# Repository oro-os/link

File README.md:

<div align="center">
	
</div>

# Oro Link

This is the Oro Link project, a set of custom PCBs, firmware, and server
infrastructure for the testing of the Oro Operating System via CI/CD pipelines.

The link is a physical board that interfaces with the ports and headers
of supported computers, devices, and boards, and runs firmware to obtain builds of
the Oro kernel and associated modules to send to the System Under Test (SUT)
for automated testing and reporting.

The Oro Link allows contributors to the Oro project direct access - via
pull requests - to test changes directly on real hardware
alongside emulated environments, allowing for changes to be tested
against niche or problematic hardware configurations.

## Project Layout

All PCBs are located in `pcb/`, where all of the server infrastructure and firmware for the PCBs
is located in `firmware/` since it's a workspace with some local dependencies (e.g. the protocol
spoken between the boards and the CI/CD daemon).

# License

<div align="center">
	
</div>

Part of the Oro Operating System project.

The Oro Link is released to the public, WARRANTY FREE
and provided AS IS. The Oro project and its contributors are NOT
responsible for any damages caused by the purchase, assembly, or operation
of the device, under any circumstances.

The Oro Link's PCB and associated custom footprints are released
under the [MIT License](LICENSE).

Unless otherwise specified, all Oro Link firmware (software code)
and all other materials are licensed under the same license.

Firmware dependencies are under their respective licenses.

The _Enter Command_ font used in part for text display is released CC-BY-4.0
by [Font End Dev (jeti)](https://fontenddev.com).

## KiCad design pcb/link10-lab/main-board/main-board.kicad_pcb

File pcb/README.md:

# Oro Link PCBs

The Oro Link PCBs are custom boards meant to interface with the
CI/CD daemon, which itself works with (at the moment, solely) GitHub
Actions runners that it manages.

These PCBs are open source and licensed under the license found in the
root of this repository.

All PCBs are designed in KiCad 7, with some technical sketches
designed in FreeCad.

There are some "legacy" PCBs here that haven't been converted to
self-standing projects (that use the `.lib/` folder). Further,
some of these PCBs are specific to individual rigs and may not
be interesting to most people.

## `link-rpi-base`

This is the base board for Raspberry Pi test rigs. It hosts
the microcontroller, network interface, etc. as well as a
board-to-board connector that interfaces with one of the
daughter boards (R-Pi version specific).

## `link-x86-obt`

> **NOTE:** This project file is a _legacy_ PCB that hasn't
> been converted to use the common components/footprints library
> in `.lib/`. You will be able to view the schematic and layout,
> but changes are more difficult to make and manage. Due to this,
> PRs that include changes to this PCB might take longer to merge.

This is the main board for testing x86/x86_64 machines using
the Oro Link CI/CD pipeline. Kernel builds are booted over PXE,
and communication is done primarily through the serial ports.

The board's form factor is designed to be mounted to the front
of an [Open Bench Table](https://openbenchtable.com/) - hence
`*-obt`.

As such, the board has two ethernet connections - one for communication
with the SUT, and the other for communication with the Link daemon.

Please see the [firmware directory](../firmware/link-firmware-x86)
for a block diagram and further explanations.

## `rj45-inverter-h410mb`

> **NOTE:** This is a rig-specific board that is likely uninteresting
> to you. It's meant to fit and cater to a very specific hardware
> configuration that most likely won't match yours. As such, this PCB
> is not required to operate a Link test rig, and probably won't
> be of use unless you match the test rig's build exactly.

> **NOTE:** This project file is a _legacy_ PCB that hasn't
> been converted to use the common components/footprints library
> in `.lib/`. You will be able to view the schematic and layout,
> but changes are more difficult to make and manage. Due to this,
> PRs that include changes to this PCB might take longer to merge.

This board has a board-mounted RJ-45 plug (_not_ socket - THT
mounted plugs were really tricky to find!) that is wired same-side
to an RJ-45 port. It's used on one of the x86 test rigs to keep the
left side of the OBT setup flush, without having an ethernet cable
poking out to the left and causing clearance issues.

## `vga-display-card-h410mb`

> **NOTE:** This is a rig-specific board that is likely uninteresting
> to you. It's meant to fit and cater to a very specific hardware
> configuration that most likely won't match yours. As such, this PCB
> is not required to operate a Link test rig, and probably won't
> be of use unless you match the test rig's build exactly.

> **NOTE:** This project file is a _legacy_ PCB that hasn't
> been converted to use the common components/footprints library
> in `.lib/`. You will be able to view the schematic and layout,
> but changes are more difficult to make and manage. Due to this,
> PRs that include changes to this PCB might take longer to merge.

This board provides power to a [VGA display](https://www.amazon.de/-/en/gp/product/B09ZDK5DMT/ref=ppx_yo_dt_b_search_asin_title?ie=UTF8&psc=1) via a PCIe x1
port on the motherboard. It also doubles as a VGA port mount
for the graphics card (which uses a cable to interface between the
card and the port), which further allows the left side of the OBT
to remain flush.

If you're interested in using the VGA display linked above, I
recommend to take it apart, desolder the transducer (beeper)
in the top corner of the board, and replace it with a resistor,
lest you go insane.

# Making a new board

If you want to add a project here, you'll need to do a few things:

1. Make the folder here. Use kebab-case, such as `link-rpi-2` instead of
   `LinkRpi2`.
2. Open KiCad and create the project in the folder. Uncheck the box that
   asks if you want to create a project folder. Preferably, name the project
   using TitleCase, such as `LinkRpi2`.
3. From any **non-legacy** project (see the above list), copy `fp-lib-table`
   and `sym-lib-table` into the new project's directory. **Restart KiCad.**
4. In both the schematic and the PCB layout, go to _File > Page Setup..._
   and change the worksheet to `${KIPRJMOD}/../.lib/Oro.kicad_wks`.
5. If you're using common sheets to re-use some of the modular schematics
   from other boards, **always use relative paths**
   (e.g. `${KIPRJMOD}/../.lib/<something>`).

If you're adding a component, it is **highly** recommended to add it from
[Ultra Librarian](https://ultralibrarian.com).

Symbols and footprints must be added to `.lib/Oro.kicad_sym` and `.lib/Oro.pretty/`,
respectively. STEP models should be placed in `.lib/step` and properly linked up
from within the footprint (usually requires manually editing the footprint after
loading it into `Oro.pretty/`).

Further, make sure to update the footprint ID in the symbol after moving it into the
Oro library.

Most importantly, **you must make sure all common fields are populated and accurate**.
These are fields found on other symbols, the names of which must match **exactly**.
For example, Mouser ID, Mfr. ID, etc.

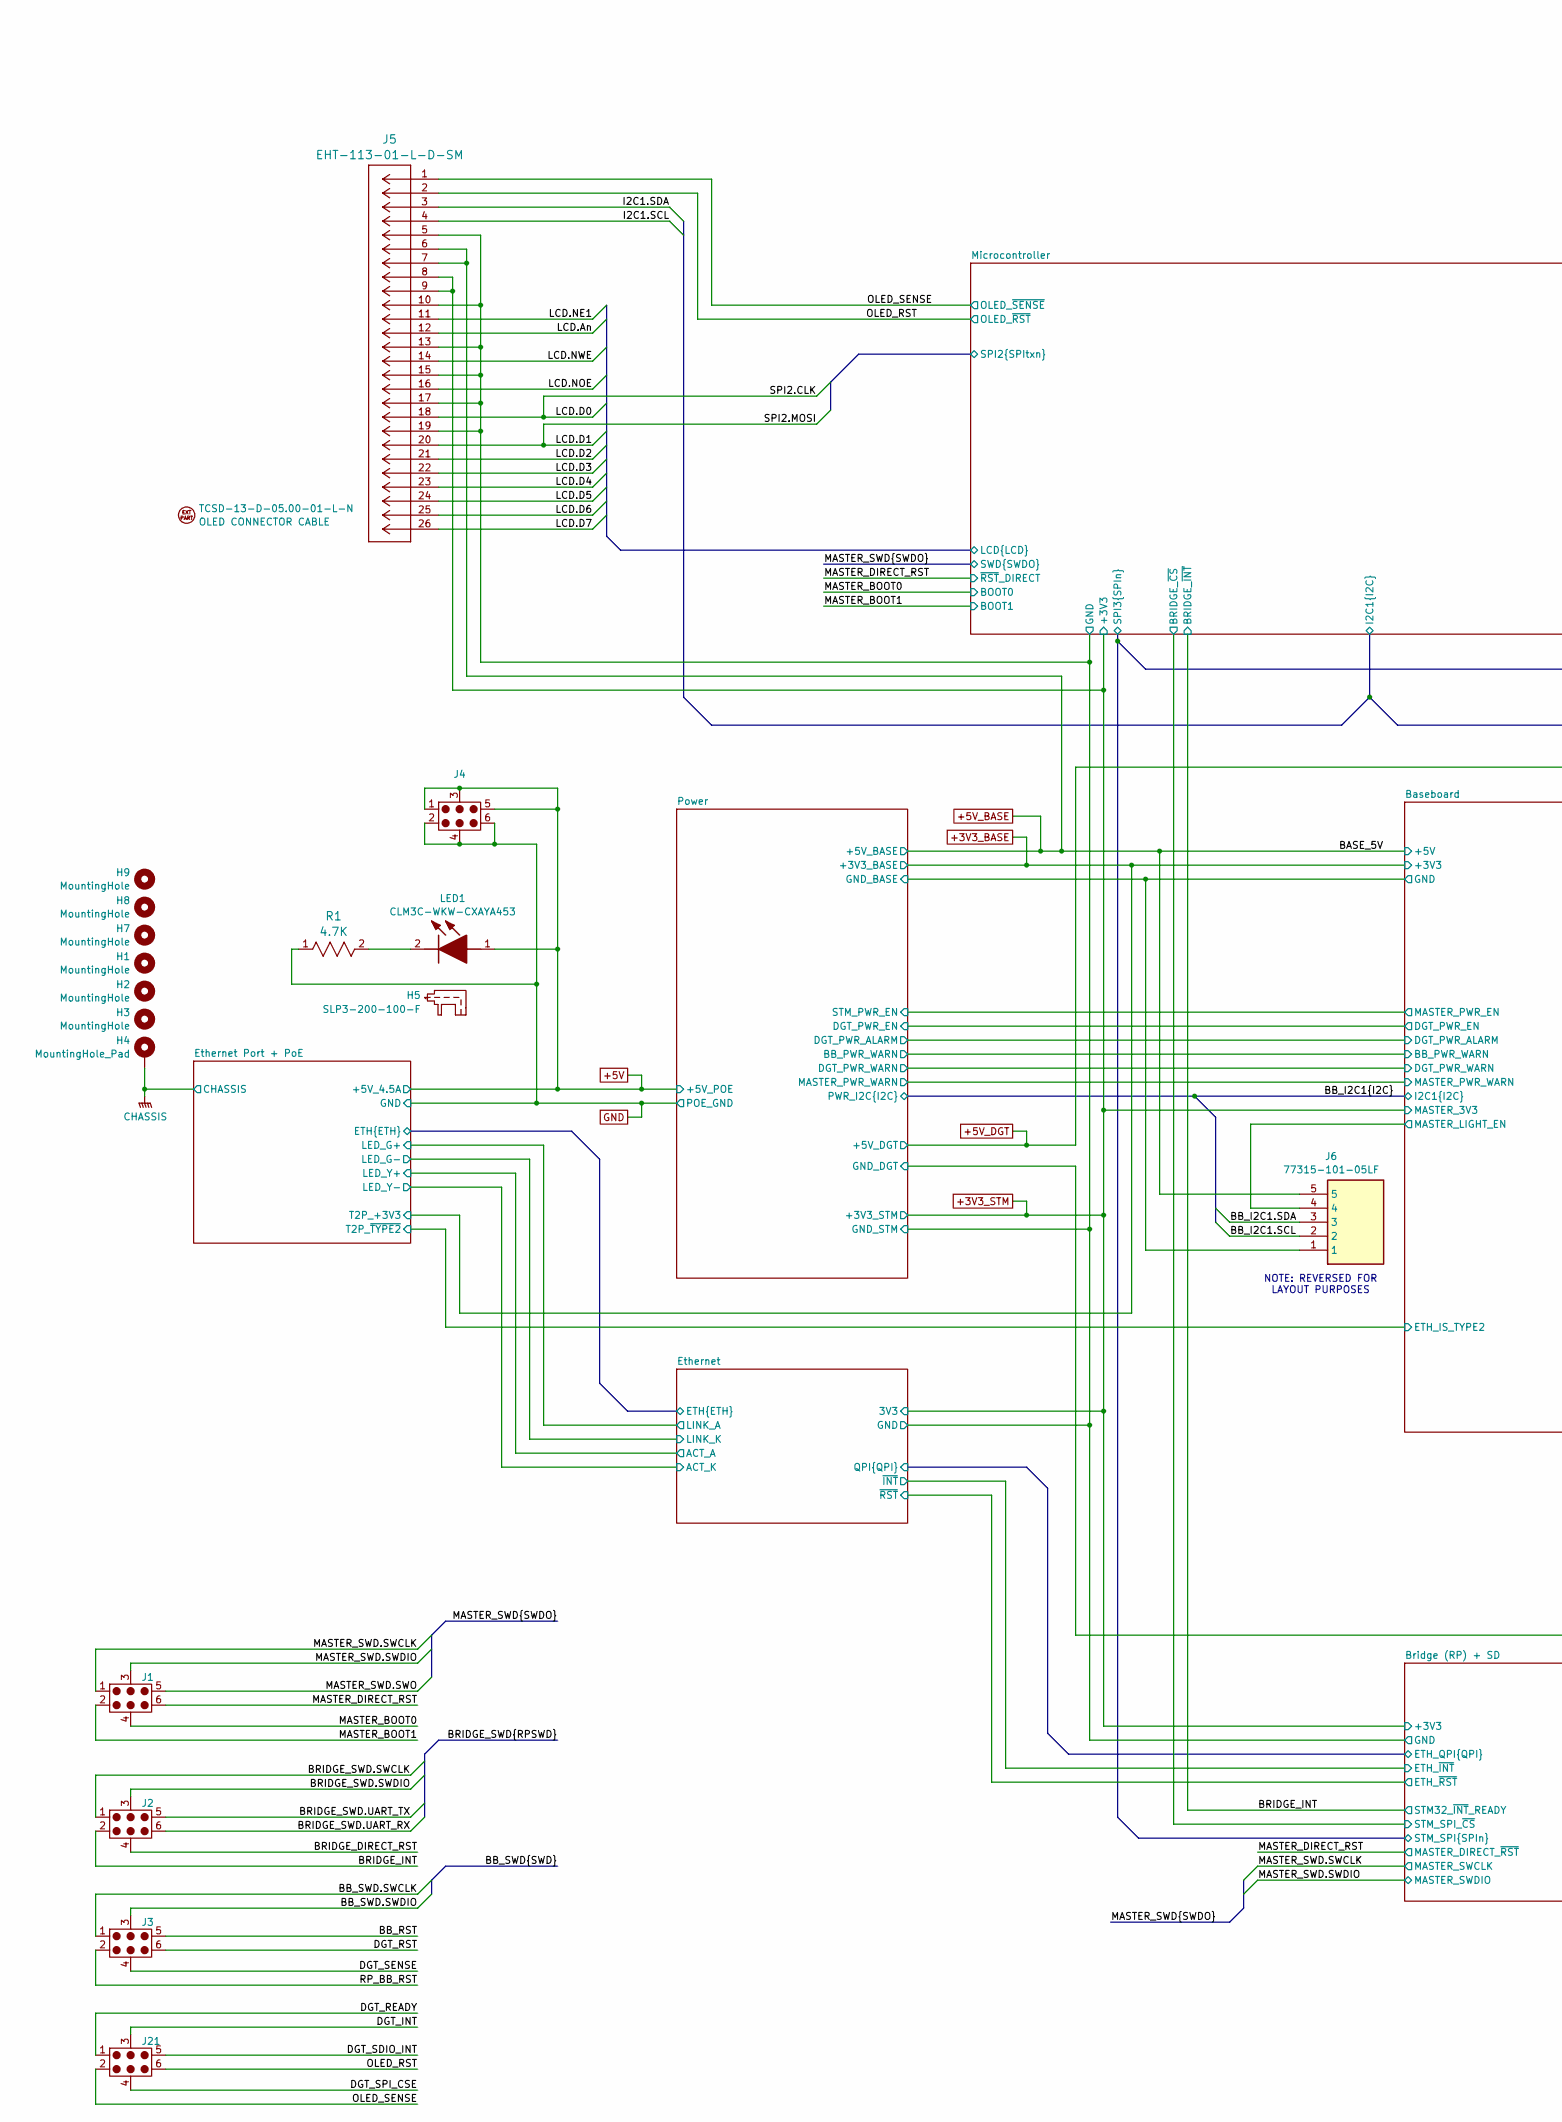
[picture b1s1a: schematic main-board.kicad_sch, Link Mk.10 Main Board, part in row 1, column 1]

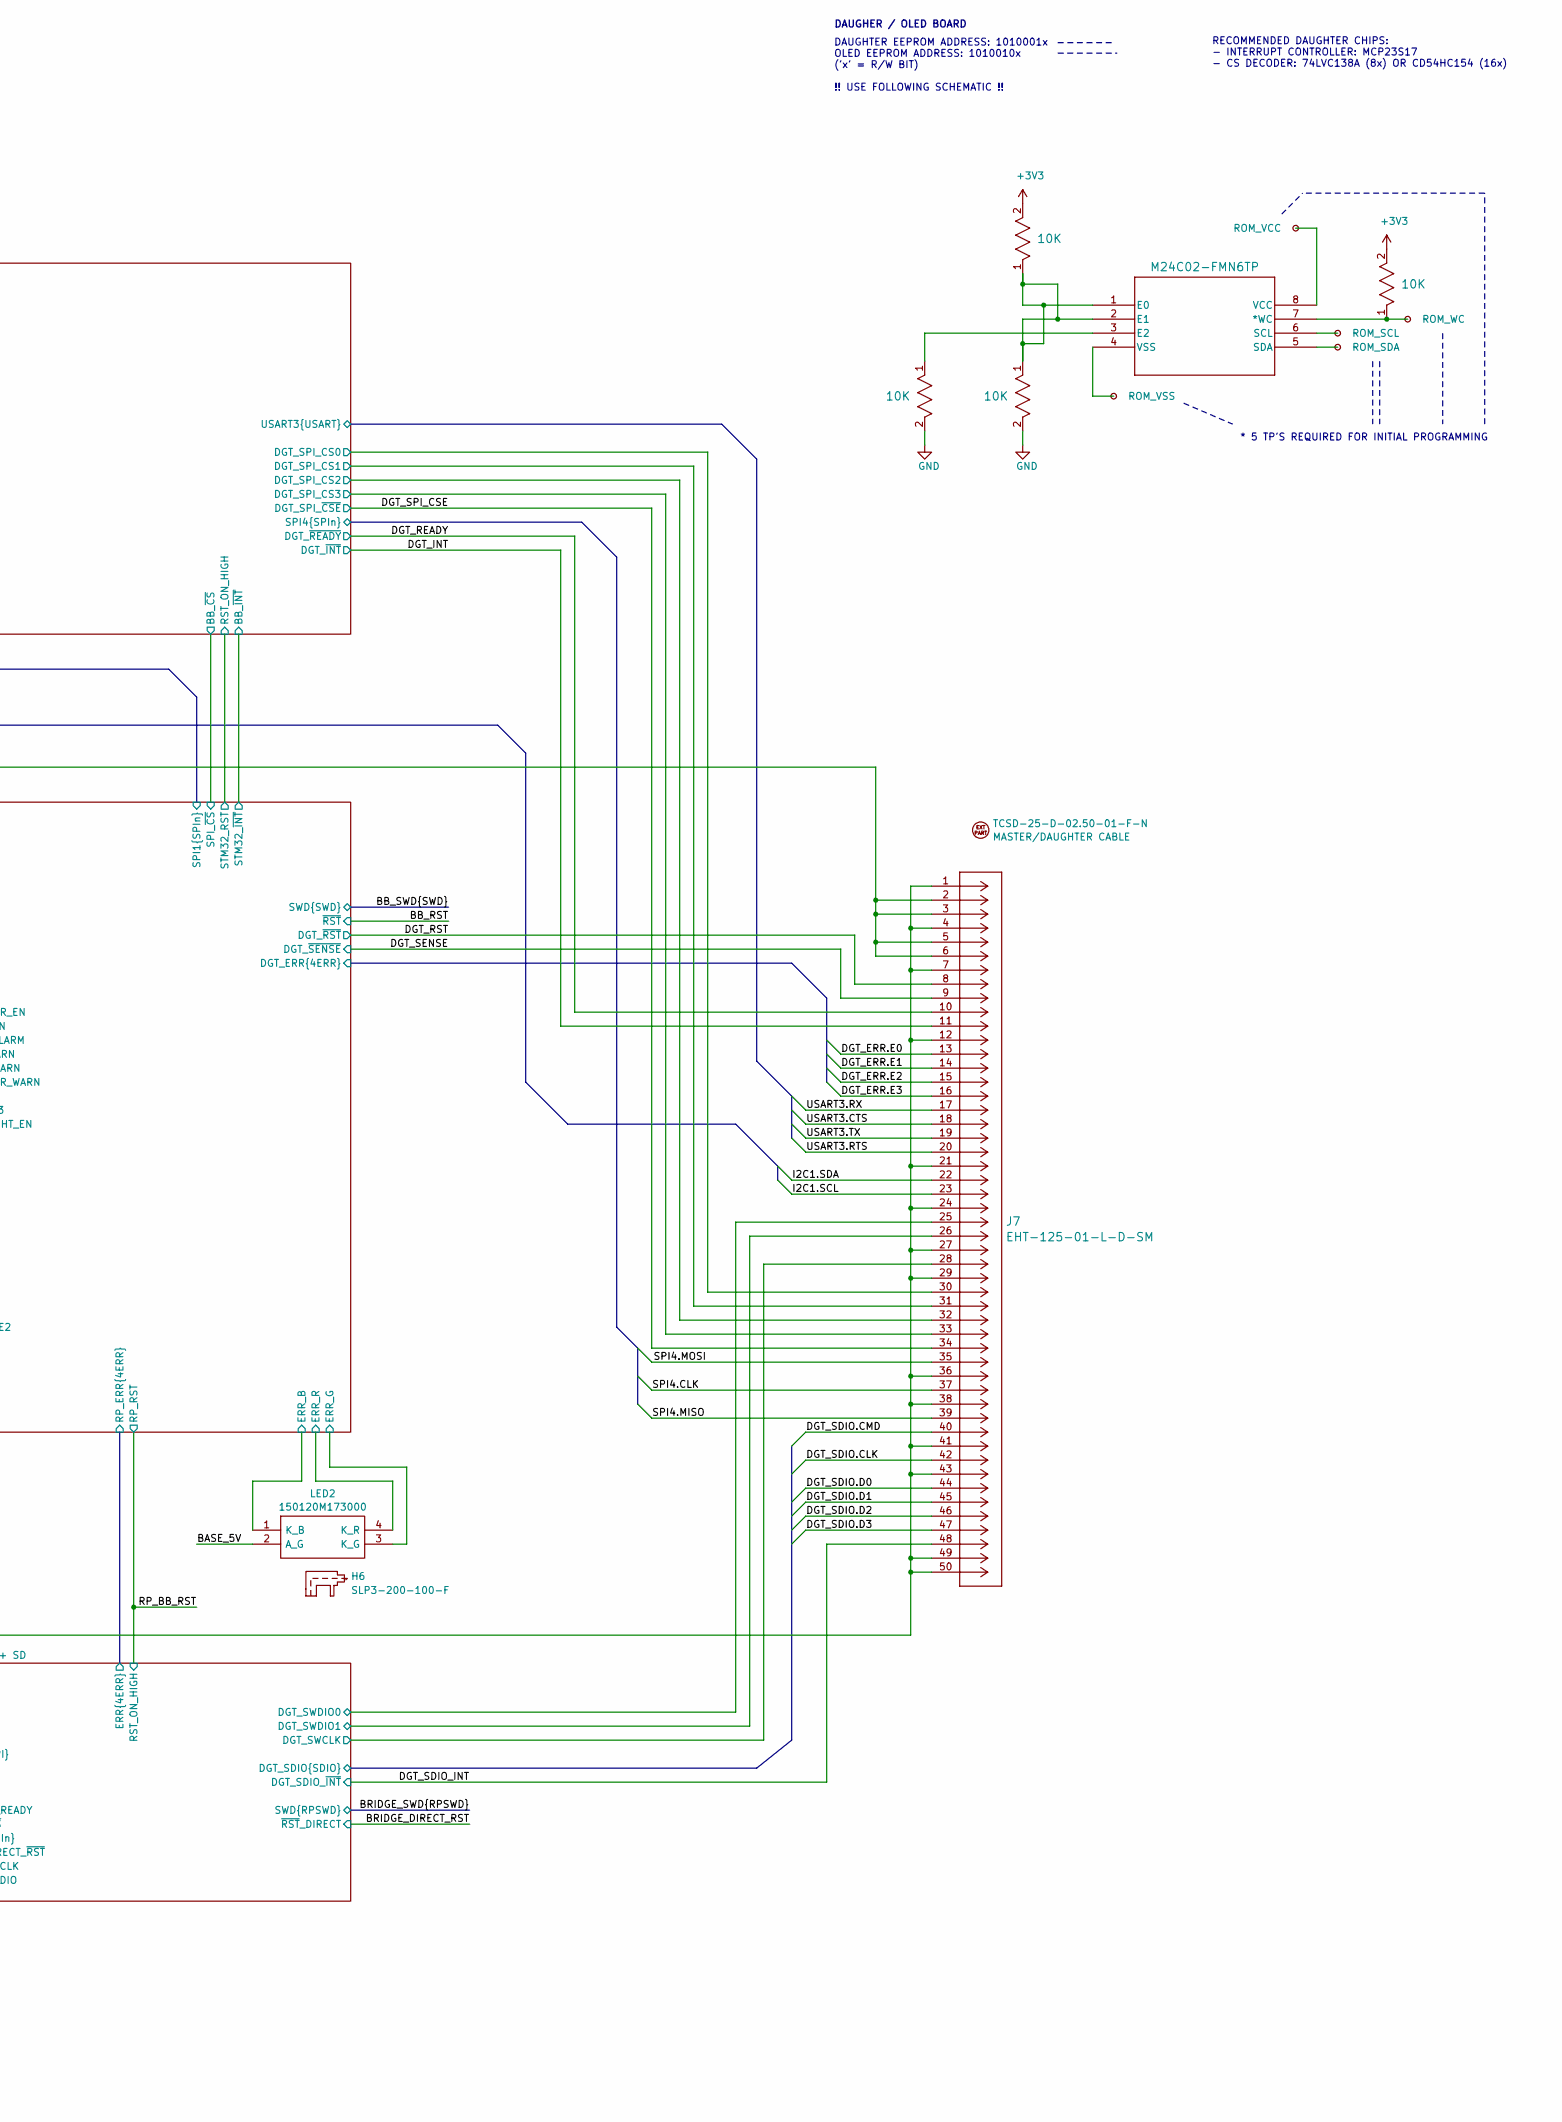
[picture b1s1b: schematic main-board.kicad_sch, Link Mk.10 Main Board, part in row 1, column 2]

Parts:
EXT6: TCSD-25-D-02.50-01-F-N; Mouser P/N 200-TCSD25D025001FN; Digi-Key P/N TCSD-25-D-02.50-01-F-N-ND
EXT7: TCSD-13-D-05.00-01-L-N; Mouser P/N 200-TCSD13D05.0001LN; Digi-Key P/N 612-TCSD-13-D-05.00-01-L-N-ND
H1, H2, H3, H7, H8, H9: MountingHole; MountingHole_3.2mm_M3
H4: MountingHole_Pad; MountingHole_3.2mm_M3_Pad_Via
H5, H6: SLP3-200-100-F; OP_0007E; Manufacturer_Part_Number SLP3-200-100-F; Mouser Part Number 749-SLP3-200-100-F
J1, J2, J3, J4, J21: CPG-81-TH-B-Pads; CPG-81-TH-B-Landing
J5: EHT-113-01-L-D-SM; OP_0007K; Mouser P/N 200-EHT11301LDSM; Digi-Key P/N EHT-113-01-L-D-SM-ND
J6: 77315-101-05LF; OP_0007G; Manufacturer_Part_Number 77315-101-05LF; Digi-Key P/N 609-77315-101-05LF-ND
J7: EHT-125-01-L-D-SM; OP_0007I; Mouser P/N 200-EHT12501LDSM; Digi-Key P/N EHT-125-01-L-D-SM-ND
LED1: CLM3C-WKW-CXAYA453; OP_00016; Manufacturer_Part_Number CLM3C-WKW-CXAYA453; Mouser Part Number 941-CLM3CWKWCXAYA453
LED2: 150120M173000; OP_00006; Manufacturer_Part_Number 150120M173000; Mouser Part Number 710-150120M173000
R1: 4.7K; OP_0001C; Mouser ID 71-CRCW04024K70FKEDH
R#1, R#2, R#3, R#4: 10K; OP_00021; DigiKey ID RMCF0402FT10K0CT-ND
TP#1: ROM_VSS; TestPoint_Pad_2.0x2.0mm
TP#2: ROM_VCC; TestPoint_Pad_2.0x2.0mm
TP#3: ROM_SCL; TestPoint_Pad_2.0x2.0mm
TP#4: ROM_SDA; TestPoint_Pad_2.0x2.0mm
TP#5: ROM_WC; TestPoint_Pad_2.0x2.0mm
U#1: M24C02-FMN6TP; OP_00074; Mouser P/N 511-M24C02-FMN6TP; Digi-Key P/N 497-15748-1-ND, 497-15748-2-ND, 497-157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

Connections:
+3V3_STM: J5.8, J5.9; also elsewhere on the board
+5V: J4.1, J4.3, J4.5, LED1.1 (A); also elsewhere on the board
+5V_BASE: J5.6, J5.7, J6.5, LED2.2 (A_G); also elsewhere on the board
+5V_DGT: J7.2, J7.3, J7.5, J7.6; also elsewhere on the board
/BB_I2C1.SCL: J6.2; also elsewhere on the board
/BB_I2C1.SDA: J6.3; also elsewhere on the board
/BB_RST: J3.5; also elsewhere on the board
/BB_SWD.SWCLK: J3.1; also elsewhere on the board
/BB_SWD.SWDIO: J3.3; also elsewhere on the board
/BRIDGE_DIRECT_RST: J2.4; also elsewhere on the board
/BRIDGE_INT: J2.2; also elsewhere on the board
/BRIDGE_SWD.SWCLK: J2.1; also elsewhere on the board
/BRIDGE_SWD.SWDIO: J2.3; also elsewhere on the board
/BRIDGE_SWD.UART_RX: J2.6; also elsewhere on the board
/BRIDGE_SWD.UART_TX: J2.5; also elsewhere on the board
/Baseboard/DGT_ERR.E0: J7.13; also elsewhere on the board
/Baseboard/DGT_ERR.E1: J7.14; also elsewhere on the board
/Baseboard/DGT_ERR.E2: J7.15; also elsewhere on the board
/Baseboard/DGT_ERR.E3: J7.16; also elsewhere on the board
/Baseboard/ERR_B: LED2.1 (K_B); also elsewhere on the board
/Baseboard/ERR_G: LED2.3 (K_G); also elsewhere on the board
/Baseboard/ERR_R: LED2.4 (K_R); also elsewhere on the board
/Baseboard/MASTER_LIGHT_EN: J6.4; also elsewhere on the board
/Bridge (RP) + SD/DGT_SDIO.CLK: J7.42; also elsewhere on the board
/Bridge (RP) + SD/DGT_SDIO.CMD: J7.40; also elsewhere on the board
/Bridge (RP) + SD/DGT_SDIO.D0: J7.44; also elsewhere on the board
/Bridge (RP) + SD/DGT_SDIO.D1: J7.45; also elsewhere on the board
/Bridge (RP) + SD/DGT_SDIO.D2: J7.46; also elsewhere on the board
/Bridge (RP) + SD/DGT_SDIO.D3: J7.47; also elsewhere on the board
/Bridge (RP) + SD/DGT_SWCLK: J7.28; also elsewhere on the board
/Bridge (RP) + SD/DGT_SWDIO0: J7.25; also elsewhere on the board
/Bridge (RP) + SD/DGT_SWDIO1: J7.26; also elsewhere on the board
/CHASSIS: H4.1 (1_1); also elsewhere on the board
/DGT_INT: J7.11, J21.3; also elsewhere on the board
/DGT_READY: J7.10, J21.1; also elsewhere on the board
/DGT_RST: J3.6, J7.8; also elsewhere on the board
/DGT_SDIO_INT: J7.48, J21.5; also elsewhere on the board
/DGT_SENSE: J3.4, J7.9; also elsewhere on the board
/DGT_SPI_CSE: J7.34, J21.4; also elsewhere on the board
/MASTER_BOOT0: J1.4; also elsewhere on the board
/MASTER_BOOT1: J1.2; also elsewhere on the board
/MASTER_DIRECT_RST: J1.6; also elsewhere on the board
/MASTER_SWD.SWCLK: J1.1; also elsewhere on the board
/MASTER_SWD.SWDIO: J1.3; also elsewhere on the board
/MASTER_SWD.SWO: J1.5; also elsewhere on the board
/Microcontroller/DGT_SPI_CS0: J7.30; also elsewhere on the board
/Microcontroller/DGT_SPI_CS1: J7.31; also elsewhere on the board
/Microcontroller/DGT_SPI_CS2: J7.32; also elsewhere on the board
/Microcontroller/DGT_SPI_CS3: J7.33; also elsewhere on the board
/Microcontroller/I2C1.SCL: J5.4, J7.23; also elsewhere on the board
/Microcontroller/I2C1.SDA: J5.3, J7.22; also elsewhere on the board
/Microcontroller/LCD.An: J5.12; also elsewhere on the board
/Microcontroller/LCD.D2: J5.21; also elsewhere on the board
/Microcontroller/LCD.D3: J5.22; also elsewhere on the board
/Microcontroller/LCD.D4: J5.23; also elsewhere on the board
/Microcontroller/LCD.D5: J5.24; also elsewhere on the board
/Microcontroller/LCD.D6: J5.25; also elsewhere on the board
/Microcontroller/LCD.D7: J5.26; also elsewhere on the board
/Microcontroller/LCD.NE1: J5.11; also elsewhere on the board
/Microcontroller/LCD.NOE: J5.16; also elsewhere on the board
/Microcontroller/LCD.NWE: J5.14; also elsewhere on the board
/Microcontroller/SPI2.CLK: J5.18; also elsewhere on the board
/Microcontroller/SPI2.MOSI: J5.20; also elsewhere on the board
/Microcontroller/SPI4.CLK: J7.37; also elsewhere on the board
/Microcontroller/SPI4.MISO: J7.39; also elsewhere on the board
/Microcontroller/SPI4.MOSI: J7.35; also elsewhere on the board
/Microcontroller/USART3.CTS: J7.18; also elsewhere on the board
/Microcontroller/USART3.RTS: J7.20; also elsewhere on the board
/Microcontroller/USART3.RX: J7.17; also elsewhere on the board
/Microcontroller/USART3.TX: J7.19; also elsewhere on the board
/OLED_RST: J5.2, J21.6; also elsewhere on the board
/OLED_SENSE: J5.1, J21.2; also elsewhere on the board
/RP_BB_RST: J3.2; also elsewhere on the board
GND: J4.2, J4.4, J4.6, J5.5, J5.10, J5.13, J5.15, J5.17, J5.19, J6.1, J7.1, J7.4, J7.7, J7.12, J7.21, J7.24, J7.27, J7.29, J7.36, J7.38, J7.41, J7.43, J7.49, J7.50, R1.1; also elsewhere on the board
unnamed: LED1.2 (K), R1.2
unnamed: R#1.1, U#1.3 (E2)
unnamed: R#1.2, R#3.2
unnamed: R#2.1, R#3.1, U#1.1 (E0), U#1.2 (E1)
unnamed: R#2.2, R#4.2
unnamed: R#4.1, TP#5.1, U#1.7 (*WC)
unnamed: TP#1.1, U#1.4 (VSS)
unnamed: TP#2.1, U#1.8 (VCC)
unnamed: TP#3.1, U#1.6 (SCL)
unnamed: TP#4.1, U#1.5 (SDA)

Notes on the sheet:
DAUGHER / OLED BOARD
DAUGHTER EEPROM ADDRESS: 1010001x OLED EEPROM ADDRESS: 1010010x ('x' = R/W BIT) !! USE FOLLOWING SCHEMATIC !!
NOTE: REVERSED FOR LAYOUT PURPOSES
* 5 TP'S REQUIRED FOR INITIAL PROGRAMMING
RECOMMENDED DAUGHTER CHIPS: - INTERRUPT CONTROLLER: MCP23S17 - CS DECODER: 74LVC138A (8x) OR CD54HC154 (16x)

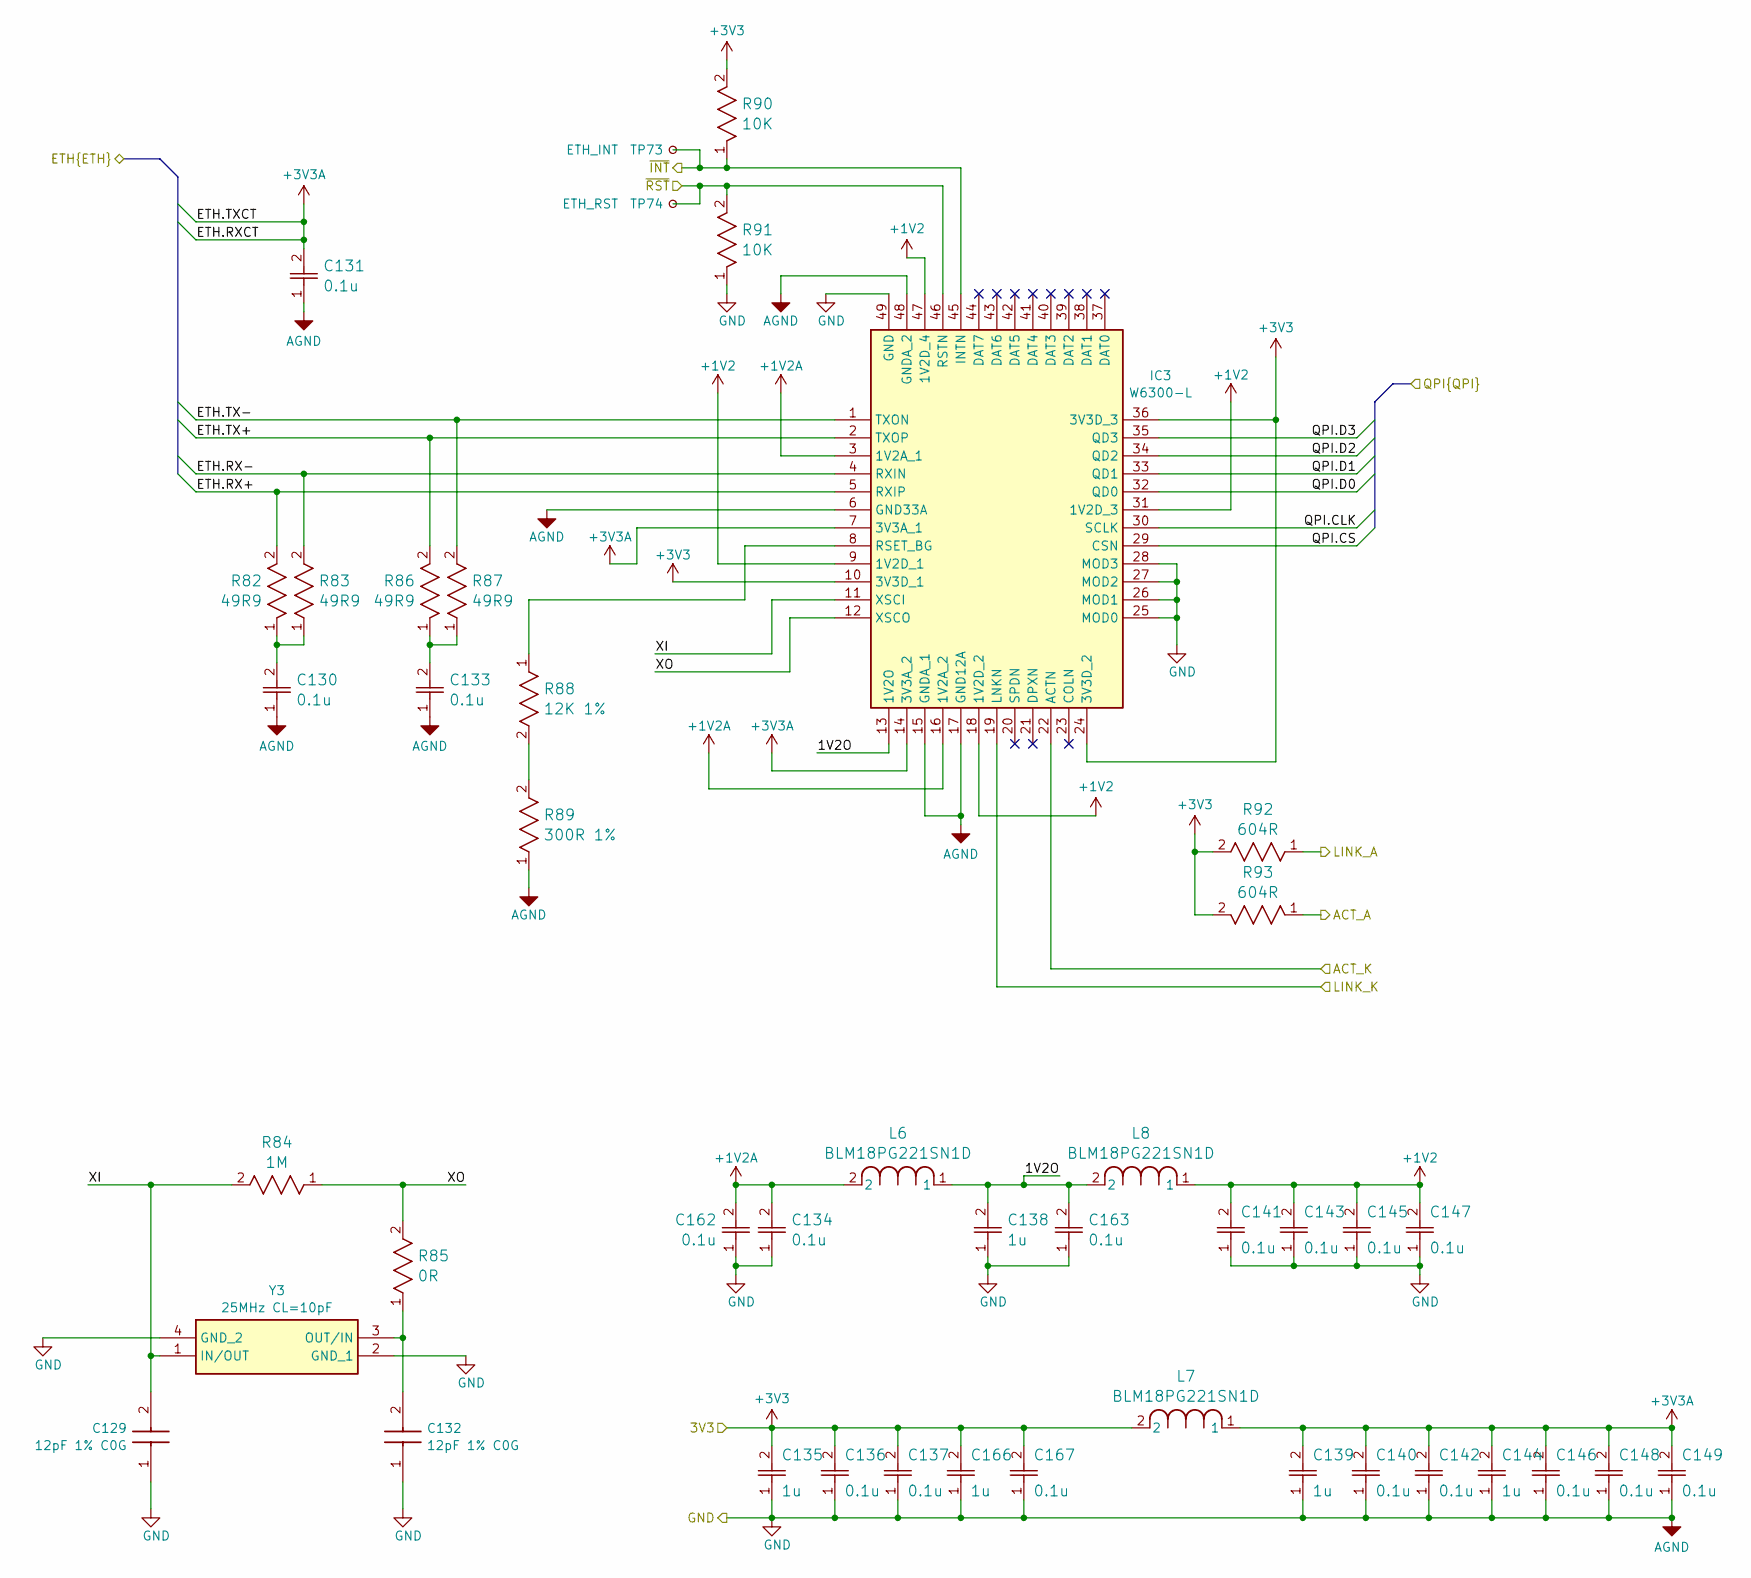
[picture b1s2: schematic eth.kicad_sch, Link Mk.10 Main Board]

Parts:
C129, C132: 12pF 1% C0G; OP_00071; Manufacturer_Part_Number GCM1555C1H120FA16J; Mouser Part Number 81-GCM1555C1H120FA6J
C130, C131, C133, C134, C136, C137, C140, C141, C142, C143, C145, C146, C147, C148, C149, C162, C163, C167: 0.1u; OP_0001Y; DigiKey ID 587-MSAST1L3YB5104KFNA01CT-ND
C135, C138, C139, C144, C166: 1u; OP_0001R; DigiKey ID 587-3766-1-ND
IC3: W6300-L; OP_00056; Manufacturer_Part_Number W6300-L
L6, L7, L8: BLM18PG221SN1D; OP_0000Y; Mouser P/N 81-BLM18PG221SN1D; DigiKey ID 490-5221-1-ND
R82, R83, R86, R87: 49R9; OP_00023; Mouser P/N 603-RT0402FRE0749R9L; Mouser URL null
R84: 1M; OP_00072; Mouser P/N 603-AC0603JR-071ML; Digi-Key P/N 311-1MLECT-ND, 311-1MLEDKR-ND, 311-1MLE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
R85: 0R; OP_0004Y; Mouser P/N 303-CQ03SAF0000T5E
R88: 12K 1%; OP_0006Y; Mouser P/N 754-RR0816P-123D; Digi-Key P/N RR08P12.0KDCT-ND, RR08P12.0KDDKR-ND, RR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
R89: 300R 1%; OP_0006Z; Mouser P/N 594-MCT06030C3000FP5; Digi-Key P/N 749-1759-1-ND, 749-1759-2-ND, 749-1759-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
R90, R91: 10K; OP_00021; DigiKey ID RMCF0402FT10K0CT-ND
R92, R93: 604R; OP_0006K; Mouser P/N 667-ERA-3AEB6040V, ERA-3AEB6040V; Digi-Key P/N P604DBCT-ND, P604DBDKR-ND, P604DBTR-ND
TP73: ETH_INT; TestPoint_Pad_D1.0mm
TP74: ETH_RST; TestPoint_Pad_D1.0mm
Y3: 25MHz CL=10pF; OP_00070; Manufacturer_Part_Number ECS-250-10-37B2-CWN-TR; Mouser Part Number 520-250-10-37B2CWNTR

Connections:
+3V3_STM: C135.2, C136.2, C137.2, C166.2, C167.2, IC3.10 (3V3D_1), IC3.24 (3V3D_2), IC3.36 (3V3D_3), L7.2, R90.2, R92.2, R93.2; also elsewhere on the board
/Bridge (RP) + SD/ETH_QPI.CLK: IC3.30 (SCLK); also elsewhere on the board
/Bridge (RP) + SD/ETH_QPI.CS: IC3.29 (CSN); also elsewhere on the board
/Bridge (RP) + SD/ETH_QPI.D0: IC3.32 (QD0); also elsewhere on the board
/Bridge (RP) + SD/ETH_QPI.D1: IC3.33 (QD1); also elsewhere on the board
/Bridge (RP) + SD/ETH_QPI.D2: IC3.34 (QD2); also elsewhere on the board
/Bridge (RP) + SD/ETH_QPI.D3: IC3.35 (QD3); also elsewhere on the board
/Bridge (RP) + SD/ETH_~INT: IC3.45 (INTN), R90.1, TP73.1 (1_1); also elsewhere on the board
/Bridge (RP) + SD/ETH_~RST: IC3.46 (RSTN), R91.2, TP74.1 (1_1); also elsewhere on the board
/Ethernet Port + PoE/ETH.RX+: IC3.5 (RXIP), R82.2; also elsewhere on the board
/Ethernet Port + PoE/ETH.RX-: IC3.4 (RXIN), R83.2; also elsewhere on the board
/Ethernet Port + PoE/ETH.TX+: IC3.2 (TXOP), R86.2; also elsewhere on the board
/Ethernet Port + PoE/ETH.TX-: IC3.1 (TXON), R87.2; also elsewhere on the board
/Ethernet Port + PoE/ETH.TXCT: C131.2, C139.2, C140.2, C142.2, C144.2, C146.2, C148.2, C149.2, IC3.7 (3V3A_1), IC3.14 (3V3A_2), L7.1; also elsewhere on the board
/Ethernet Port + PoE/LED_G+: R92.1; also elsewhere on the board
/Ethernet Port + PoE/LED_G-: IC3.19 (LNKN); also elsewhere on the board
/Ethernet Port + PoE/LED_Y+: R93.1; also elsewhere on the board
/Ethernet Port + PoE/LED_Y-: IC3.22 (ACTN); also elsewhere on the board
/Ethernet/1V2O: C138.2, C163.2, IC3.13 (1V2O), L6.1, L8.2
/Ethernet/+1V2: C141.2, C143.2, C145.2, C147.2, IC3.9 (1V2D_1), IC3.18 (1V2D_2), IC3.31 (1V2D_3), IC3.47 (1V2D_4), L8.1
/Ethernet/+1V2A: C134.2, C162.2, IC3.3 (1V2A_1), IC3.16 (1V2A_2), L6.2
/Ethernet/XI: C129.2, IC3.11 (XSCI), R84.2, Y3.1 (IN/OUT)
/Ethernet/XO: IC3.12 (XSCO), R84.1, R85.2
GND: C129.1, C130.1, C131.1, C132.1, C133.1, C134.1, C135.1, C136.1, C137.1, C138.1, C139.1, C140.1, C141.1, C142.1, C143.1, C144.1, C145.1, C146.1, C147.1, C148.1, C149.1, C162.1, C163.1, C166.1, C167.1, IC3.6 (GND33A), IC3.15 (GNDA_1), IC3.17 (GND12A), IC3.25 (MOD0), IC3.26 (MOD1), IC3.27 (MOD2), IC3.28 (MOD3), IC3.48 (GNDA_2), IC3.49 (GND), R89.1, R91.1, Y3.2 (GND_1), Y3.4 (GND_2); also elsewhere on the board
unnamed: C130.2, R82.1, R83.1
unnamed: C133.2, R86.1, R87.1
unnamed: IC3.8 (RSET_BG), R88.1
unnamed: R88.2, R89.2
unnamed: C132.2, R85.1, Y3.3 (OUT/IN)

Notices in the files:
pcb/atx24-power/atx24_power.kicad_pcb:
Copyright (C) 2025, MPL-2.0
pcb/atx24-power/atx24_power.kicad_sch:
Copyright 2025, MPL 2.0
pcb/link/power.kicad_sch:
Copyright 2023-2025, MPL 2.0
pcb/link10-lab/lights/lights.kicad_pcb:
Copyright 2023-2026, MPL 2.0
(C) 2026, JOSH JUNON
